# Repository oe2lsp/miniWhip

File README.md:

# miniWhip
e-field antenna optimized for low frequencies  
lower corner frequency limited by bias-T, with 470mH below 10kHz  
upper corner frequency arround 70MHz  
supply Voltage 5-15V  

## Schematic

## Pictures

## License
project is published unter GPLv2 license

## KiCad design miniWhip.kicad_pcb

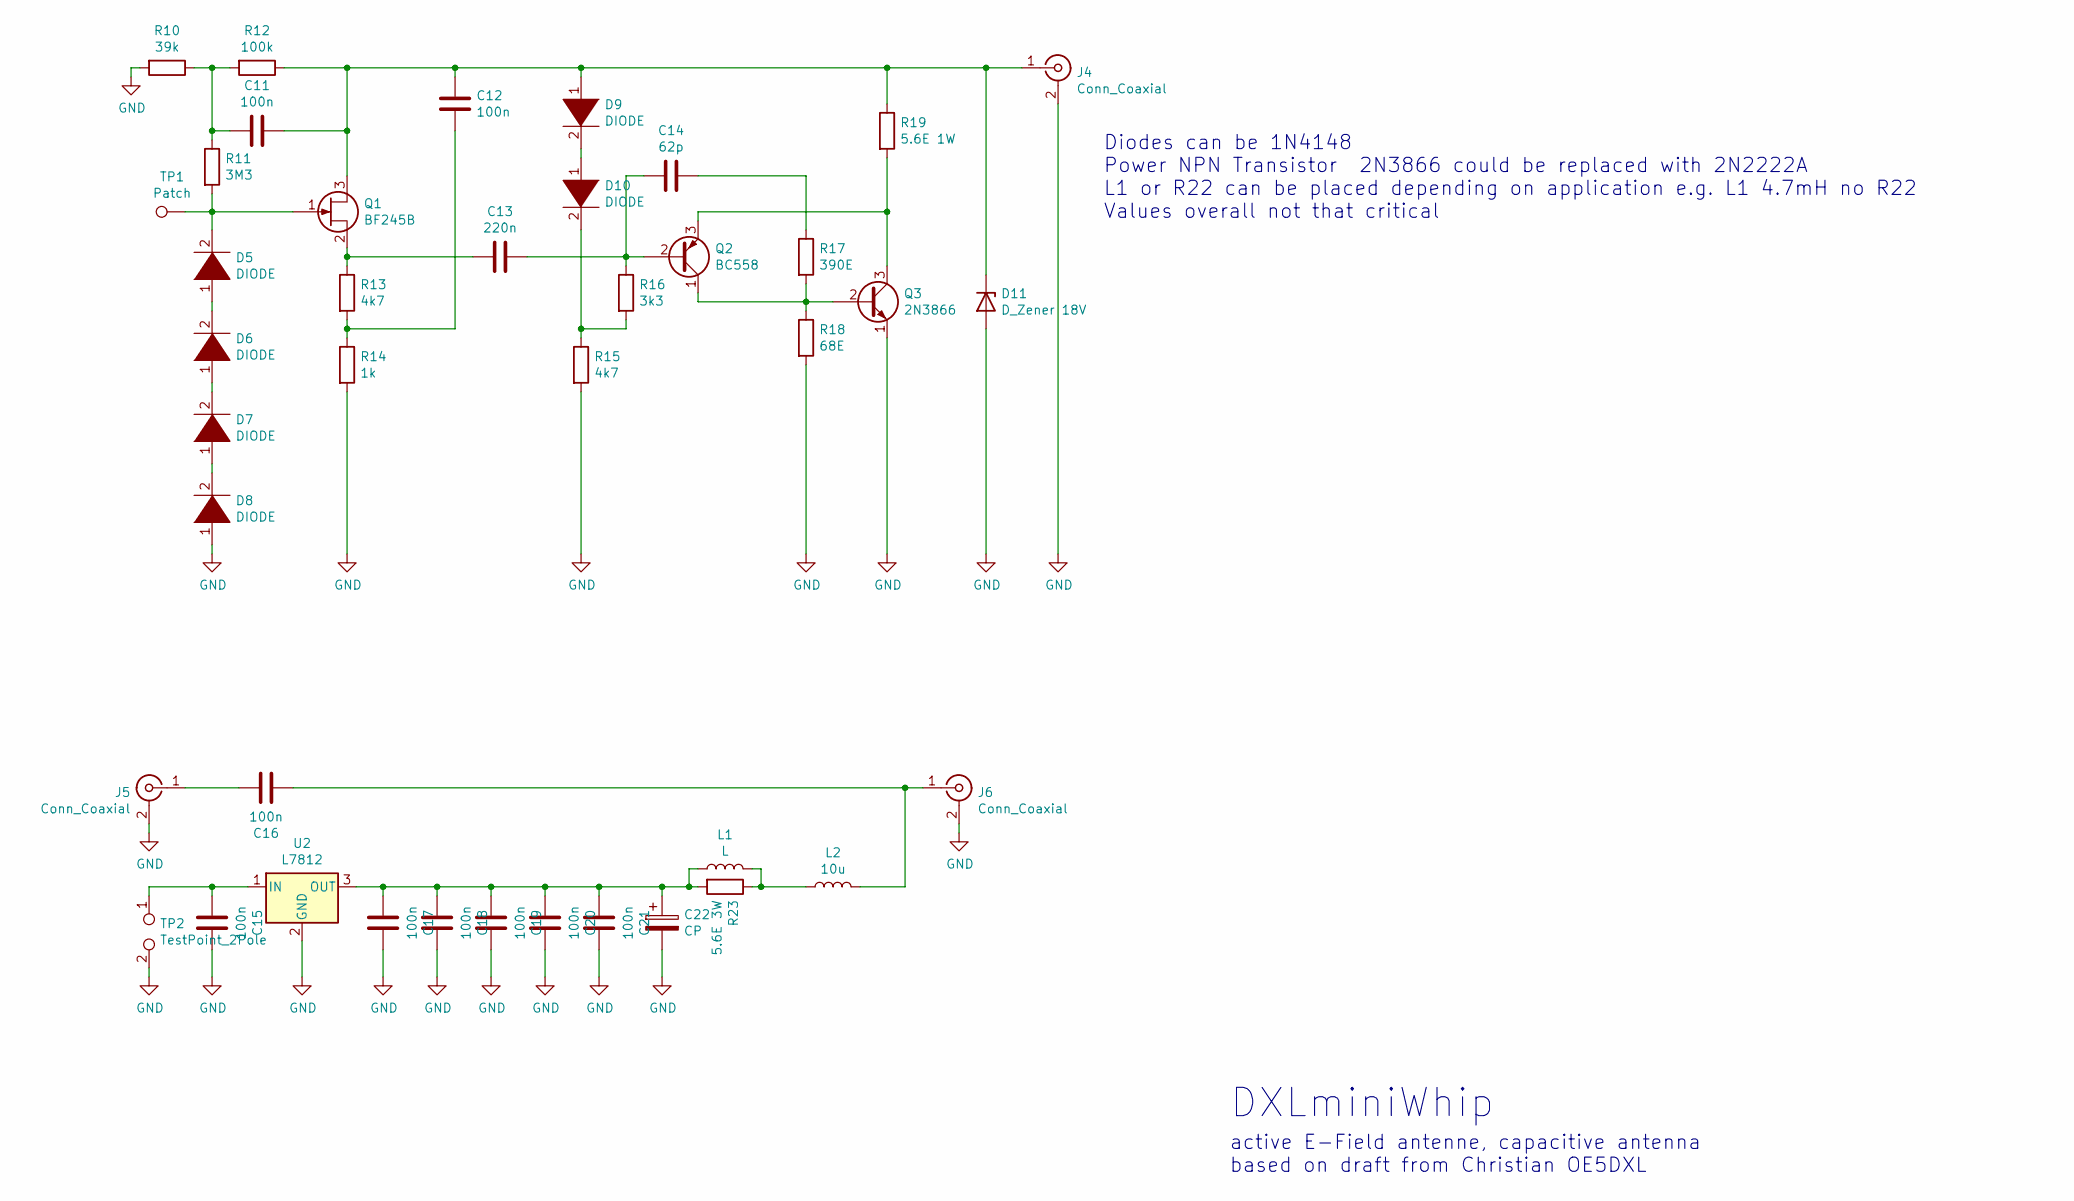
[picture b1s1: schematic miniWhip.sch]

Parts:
C11, C12, C15, C16, C17, C18, C19, C20, C21: 100n; C_0603_1608Metric_Pad1.08x0.95mm_HandSolder
C13: 220n; C_0603_1608Metric_Pad1.08x0.95mm_HandSolder
C14: 62p; C_0603_1608Metric_Pad1.08x0.95mm_HandSolder
C22: CP; CP_Elec_10x10
D5, D6, D7, D8, D9, D10: DIODE; D_1206_3216Metric_Pad1.42x1.75mm_HandSolder
D11: D_Zener 18V; D_1206_3216Metric_Pad1.42x1.75mm_HandSolder
J4, J5, J6: Conn_Coaxial; SMA_Amphenol_132289_EdgeMount
L1: L; L_12x12mm_H8mm
L2: 10u; L_2816_7142Metric_Pad3.20x4.45mm_HandSolder
Q1: BF245B; TO-92
Q2: BC558; TO-92
Q3: 2N3866; TO-39-3
R10: 39k; R_0603_1608Metric_Pad0.98x0.95mm_HandSolder
R11: 3M3; R_0603_1608Metric_Pad0.98x0.95mm_HandSolder
R12: 100k; R_0603_1608Metric_Pad0.98x0.95mm_HandSolder
R13, R15: 4k7; R_0603_1608Metric_Pad0.98x0.95mm_HandSolder
R14: 1k; R_0603_1608Metric_Pad0.98x0.95mm_HandSolder
R16: 3k3; R_0603_1608Metric_Pad0.98x0.95mm_HandSolder
R17: 390E; R_0603_1608Metric_Pad0.98x0.95mm_HandSolder
R18: 68E; R_0603_1608Metric_Pad0.98x0.95mm_HandSolder
R19: 5.6E 1W; R_Axial_DIN0617_L17.0mm_D6.0mm_P7.62mm_Vertical
R23: 5.6E 3W; R_Axial_DIN0617_L17.0mm_D6.0mm_P7.62mm_Vertical
TP1: Patch; TestPoint_Loop_D2.60mm_Drill1.6mm_Beaded
TP2: TestPoint_2Pole; TestPoint_2Pads_Pitch2.54mm_Drill0.8mm
U2: L7812; TO-220-3_Vertical

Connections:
GND: C15.2, C17.2, C18.2, C19.2, C20.2, C21.2, C22.2, D8.1 (K), D11.2 (A), J4.2 (Ext), J5.2 (Ext), J6.2 (Ext), Q3.1 (E), R10.2, R14.2, R15.2, R18.2, TP2.2, U2.2 (GND)
unnamed: C11.1, C12.2, D9.1 (K), D11.1 (K), J4.1 (In), Q1.3 (D), R12.1, R19.1
unnamed: C11.2, R10.1, R11.1, R12.2
unnamed: C12.1, R13.2, R14.1
unnamed: C13.1, Q1.2 (S), R13.1
unnamed: C13.2, C14.1, Q2.2 (B), R16.1
unnamed: C14.2, R17.1
unnamed: C15.1, TP2.1, U2.1 (IN)
unnamed: C16.1, J6.1 (In), L2.2
unnamed: C16.2, J5.1 (In)
unnamed: C17.1, C18.1, C19.1, C20.1, C21.1, C22.1, L1.1, R23.2, U2.3 (OUT)
unnamed: D5.1 (K), D6.2 (A)
unnamed: D5.2 (A), Q1.1 (G), R11.2, TP1.1
unnamed: D6.1 (K), D7.2 (A)
unnamed: D7.1 (K), D8.2 (A)
unnamed: D9.2 (A), D10.1 (K)
unnamed: D10.2 (A), R15.1, R16.2
unnamed: L1.2, L2.1, R23.1
unnamed: Q2.1 (C), Q3.2 (B), R17.2, R18.1
unnamed: Q2.3 (E), Q3.3 (C), R19.2

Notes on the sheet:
Diodes can be 1N4148 Power NPN Transistor 2N3866 could be replaced with 2N2222A L1 or R22 can be placed depending on application e.g. L1 4.7mH no R22 Values overall not that critical
DXLminiWhip
active E-Field antenne, capacitive antenna based on draft from Christian OE5DXL

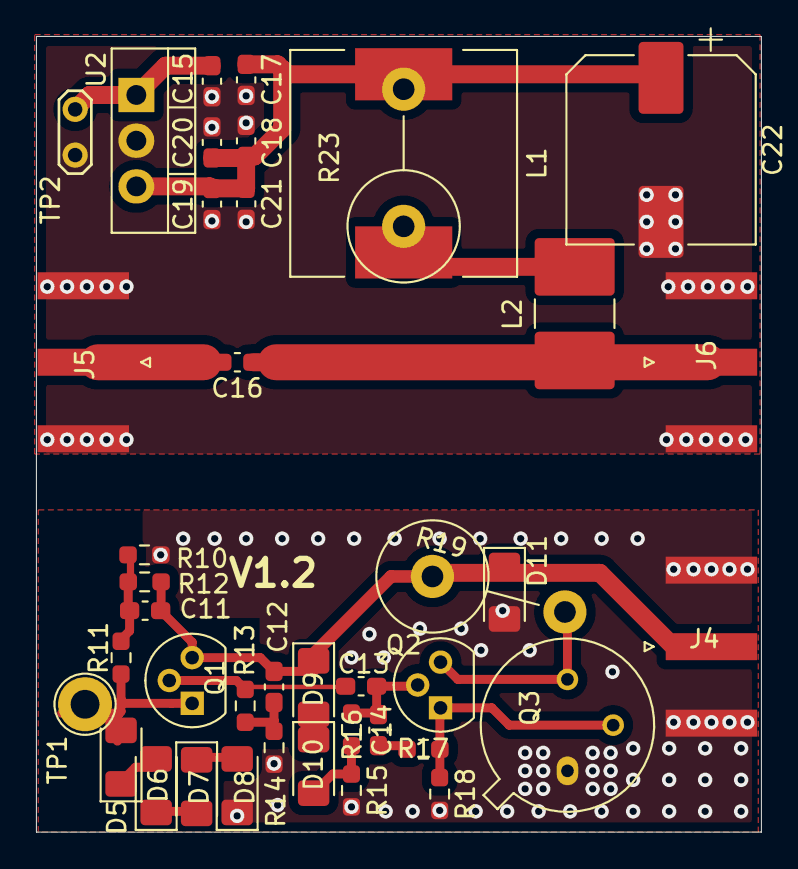
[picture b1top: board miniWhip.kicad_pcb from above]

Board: 2 copper layers, 40.3 x 44.2 mm, 41 parts (0 on the bottom side), 20 nets.

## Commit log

2021-11-18 miniWhip_v1.2
2021-11-22 Create LICENSE
2021-11-22 add svg
